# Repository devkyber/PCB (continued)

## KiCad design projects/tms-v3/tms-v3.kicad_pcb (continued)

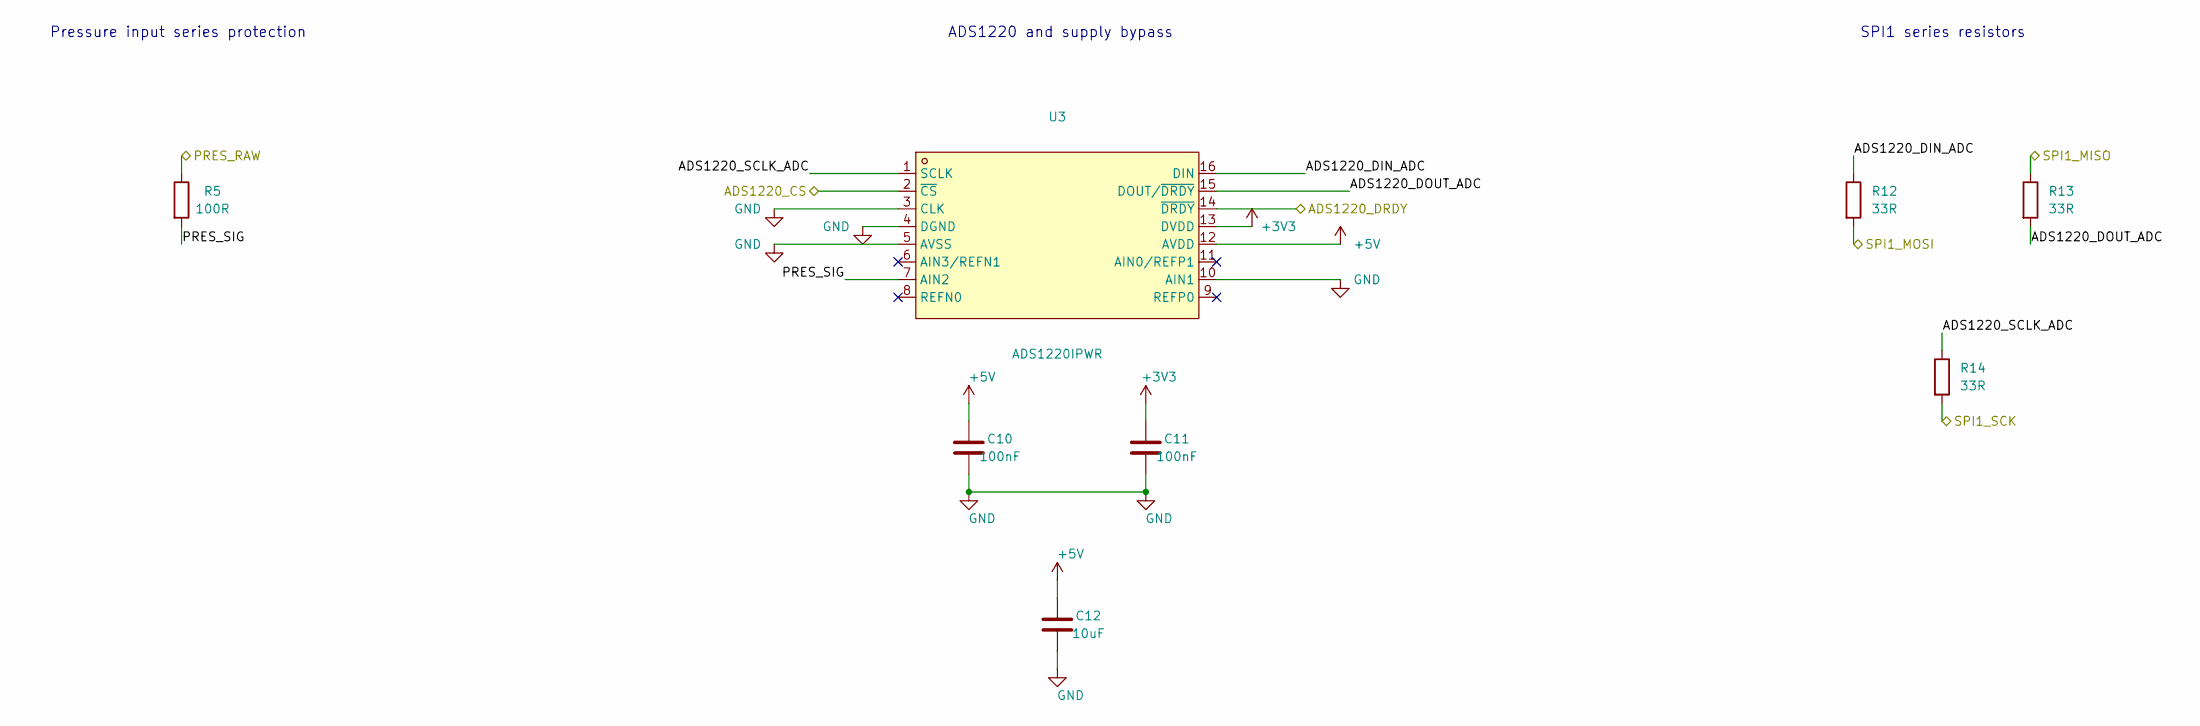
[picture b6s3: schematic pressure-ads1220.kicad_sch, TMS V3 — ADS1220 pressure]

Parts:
C10, C11: 100nF; C_0402_1005Metric
C12: 10uF; C_0805_2012Metric
R5: 100R; R_0402_1005Metric
R12, R13, R14: 33R; R_0402_1005Metric
U3: ADS1220IPWR; TSSOP-16_L5.0-W4.4-P0.65-LS6.4-BL

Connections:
+3V3: C11.1, U3.13 (DVDD); also elsewhere on the board
+5V: C10.1, C12.1, U3.12 (AVDD); also elsewhere on the board
ADS1220 pressure/ADS1220_DIN_ADC: R12.1, U3.16 (DIN)
ADS1220 pressure/ADS1220_DOUT_ADC: R13.2, U3.15 (DOUT/~DRDY)
ADS1220 pressure/ADS1220_SCLK_ADC: R14.1, U3.1 (SCLK)
ADS1220 pressure/PRES_SIG: R5.2, U3.7 (AIN2)
ADS1220_CS: U3.2 (~CS); also elsewhere on the board
ADS1220_DRDY: U3.14 (~DRDY); also elsewhere on the board
GND: C10.2, C11.2, C12.2, U3.3 (CLK), U3.4 (DGND), U3.5 (AVSS), U3.10 (AIN1); also elsewhere on the board
PRES_RAW: R5.1; also elsewhere on the board
SPI1_MISO: R13.1; also elsewhere on the board
SPI1_MOSI: R12.2; also elsewhere on the board
SPI1_SCK: R14.2; also elsewhere on the board

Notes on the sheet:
Pressure input series protection
ADS1220 and supply bypass
SPI1 series resistors

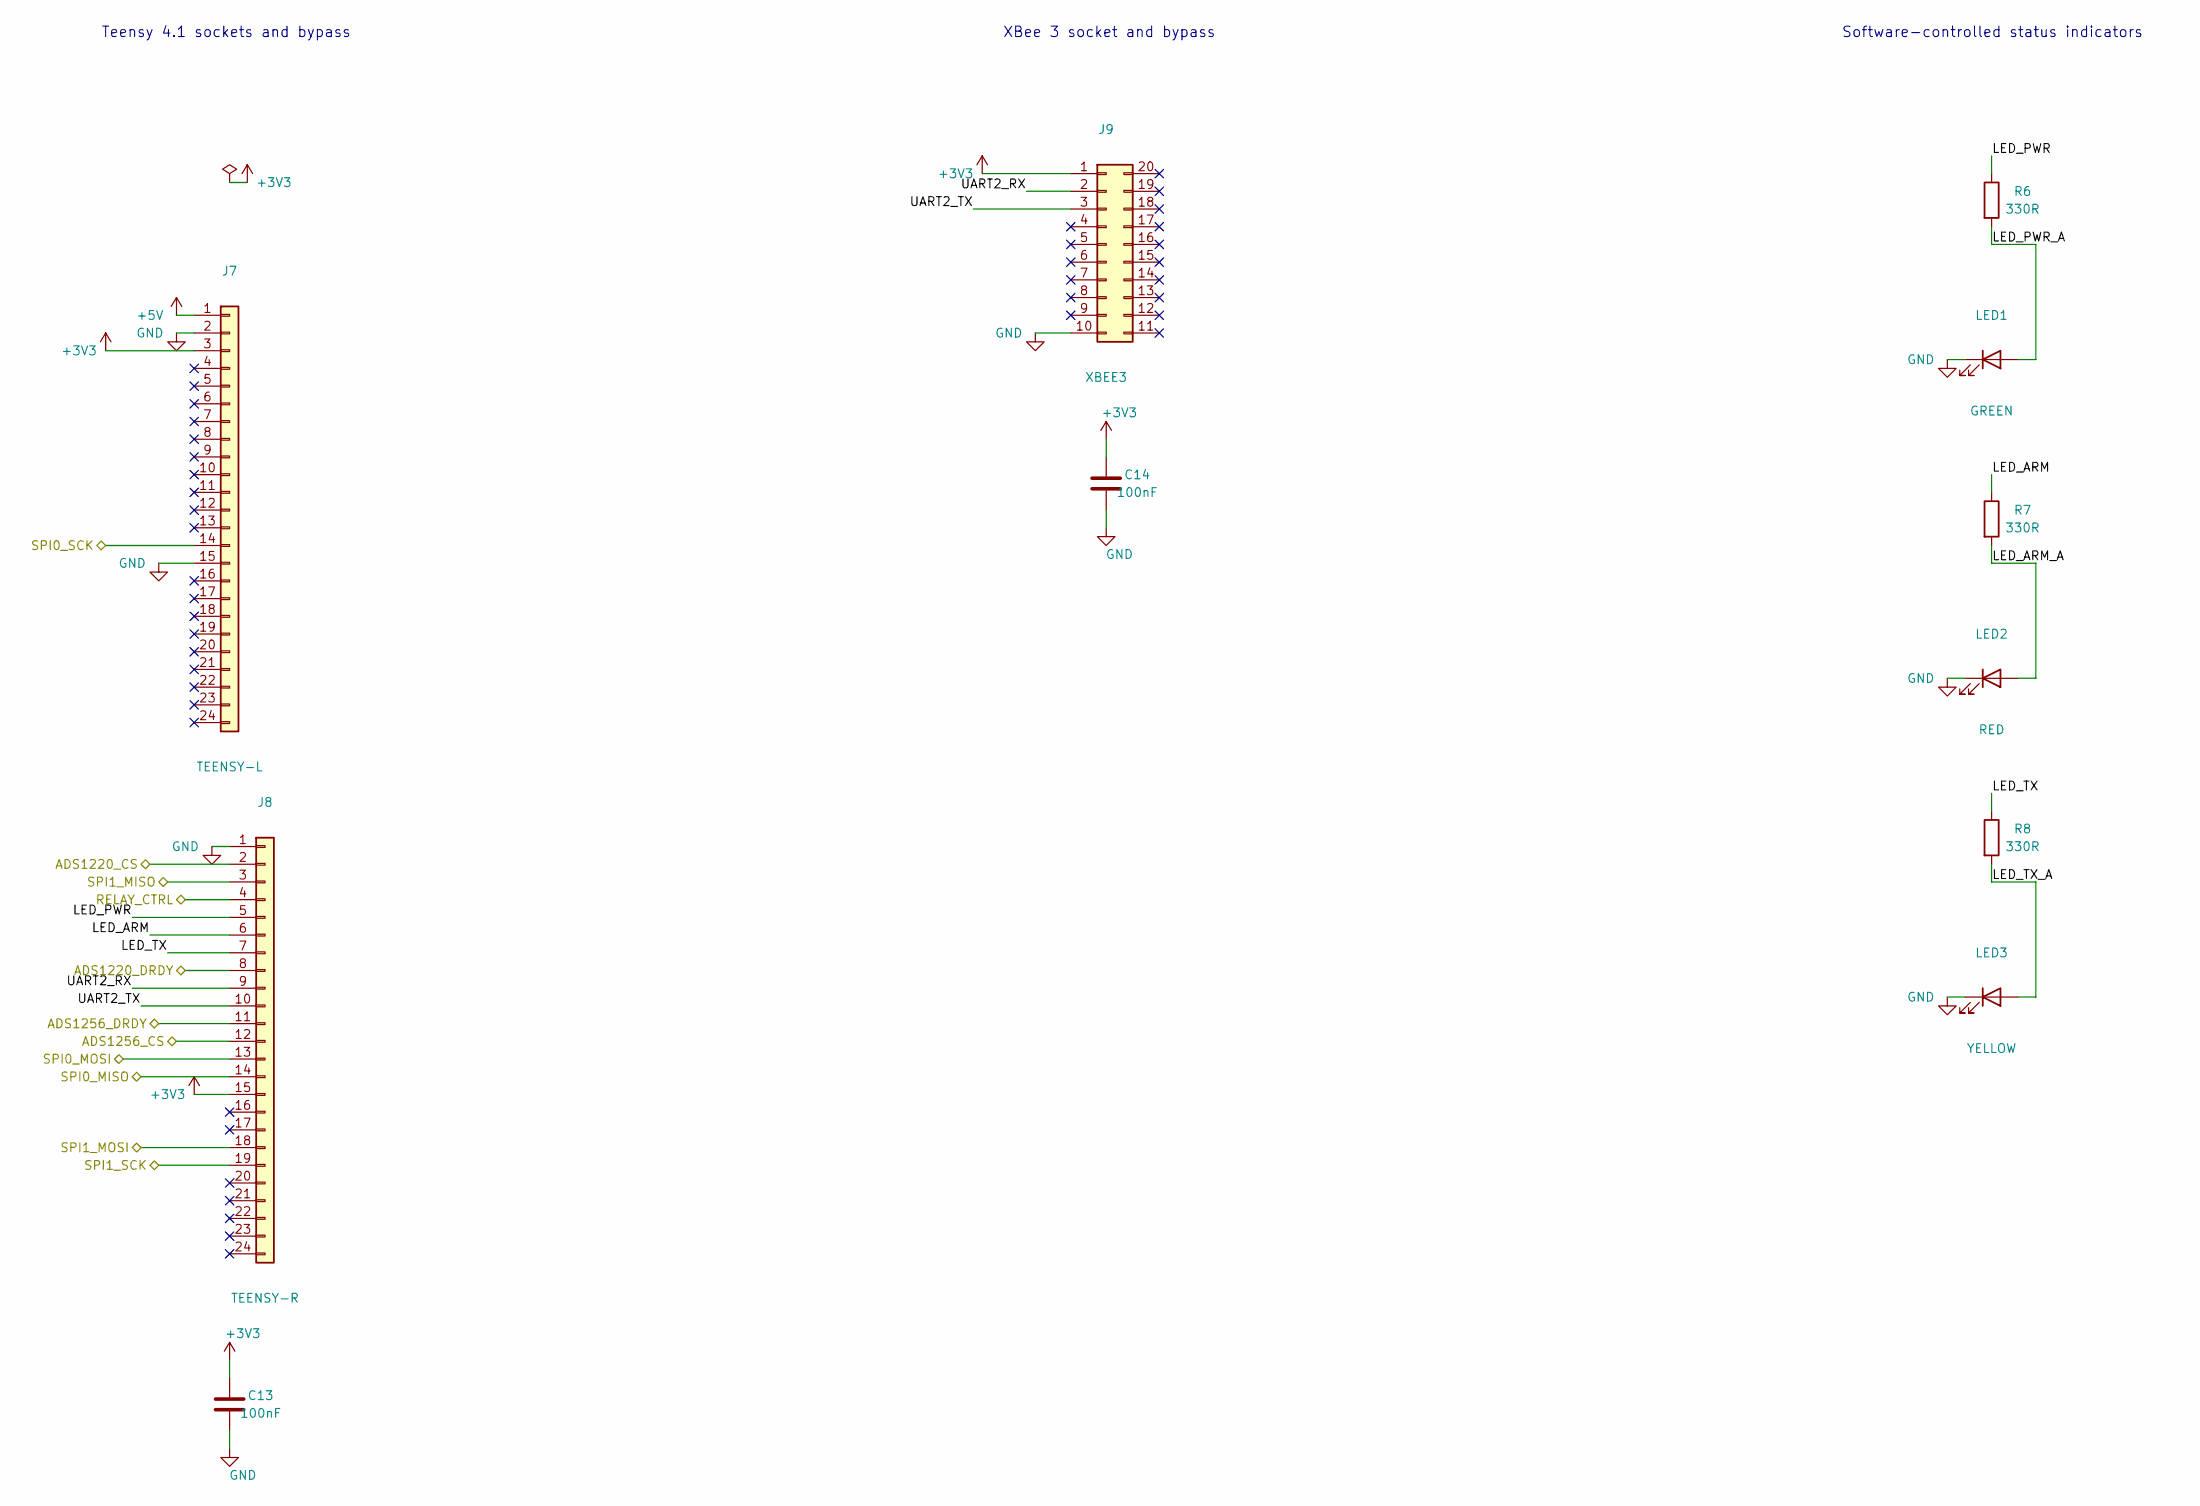
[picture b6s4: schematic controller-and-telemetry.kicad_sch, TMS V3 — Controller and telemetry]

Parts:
C13, C14: 100nF; C_0603_1608Metric
J7: TEENSY-L; PinSocket_1x24_P2.54mm_Vertical
J8: TEENSY-R; PinSocket_1x24_P2.54mm_Vertical
J9: XBEE3; XBee_THT_20pin_P2.00mm
LED1: GREEN; LED_0603_1608Metric
LED2: RED; LED_0603_1608Metric
LED3: YELLOW; LED_0603_1608Metric
R6, R7, R8: 330R; R_0402_1005Metric

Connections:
+3V3: C13.1, C14.1, J7.3, J8.15, J9.1; also elsewhere on the board
+5V: J7.1; also elsewhere on the board
ADS1220_CS: J8.2; also elsewhere on the board
ADS1220_DRDY: J8.8; also elsewhere on the board
ADS1256_CS: J8.12; also elsewhere on the board
ADS1256_DRDY: J8.11; also elsewhere on the board
Controller and telemetry/LED_ARM: J8.6, R7.1
Controller and telemetry/LED_ARM_A: LED2.2 (A), R7.2
Controller and telemetry/LED_PWR: J8.5, R6.1
Controller and telemetry/LED_PWR_A: LED1.2 (A), R6.2
Controller and telemetry/LED_TX: J8.7, R8.1
Controller and telemetry/LED_TX_A: LED3.2 (A), R8.2
Controller and telemetry/UART2_RX: J8.9, J9.2
Controller and telemetry/UART2_TX: J8.10, J9.3
GND: C13.2, C14.2, J7.2, J7.15, J8.1, J9.10, LED1.1 (K), LED2.1 (K), LED3.1 (K); also elsewhere on the board
RELAY_CTRL: J8.4; also elsewhere on the board
SPI0_MISO: J8.14; also elsewhere on the board
SPI0_MOSI: J8.13; also elsewhere on the board
SPI0_SCK: J7.14; also elsewhere on the board
SPI1_MISO: J8.3; also elsewhere on the board
SPI1_MOSI: J8.18; also elsewhere on the board
SPI1_SCK: J8.19; also elsewhere on the board

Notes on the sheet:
Teensy 4.1 sockets and bypass
XBee 3 socket and bypass
Software-controlled status indicators

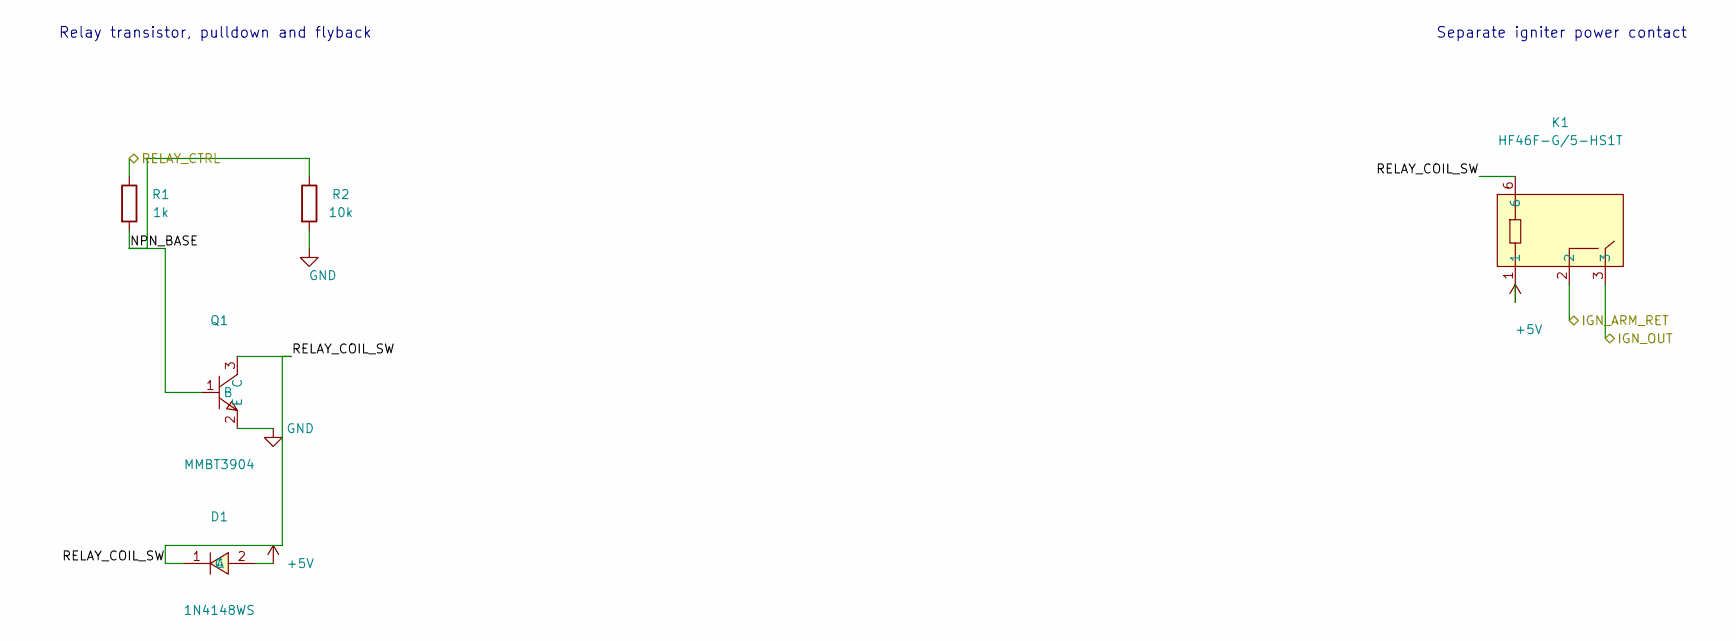
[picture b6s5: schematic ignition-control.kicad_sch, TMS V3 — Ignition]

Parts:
D1: 1N4148WS; SOD-323_L1.8-W1.3-LS2.5-RD-1
K1: HF46F-G/5-HS1T; RELAYS-TH_HF46F-G-XX-HS1-XXX
Q1: MMBT3904; SOT-23-3_L2.9-W1.3-P1.90-LS2.4-BR
R1: 1k; R_0402_1005Metric
R2: 10k; R_0402_1005Metric

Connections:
+5V: D1.2 (A), K1.1; also elsewhere on the board
GND: Q1.2 (E), R2.2; also elsewhere on the board
IGN_ARM_RET: K1.2; also elsewhere on the board
IGN_OUT: K1.3; also elsewhere on the board
Ignition/NPN_BASE: Q1.1 (B), R1.2, R2.1
Ignition/RELAY_COIL_SW: D1.1 (C), K1.6, Q1.3 (C)
RELAY_CTRL: R1.1; also elsewhere on the board

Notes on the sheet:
Relay transistor, pulldown and flyback
Separate igniter power contact

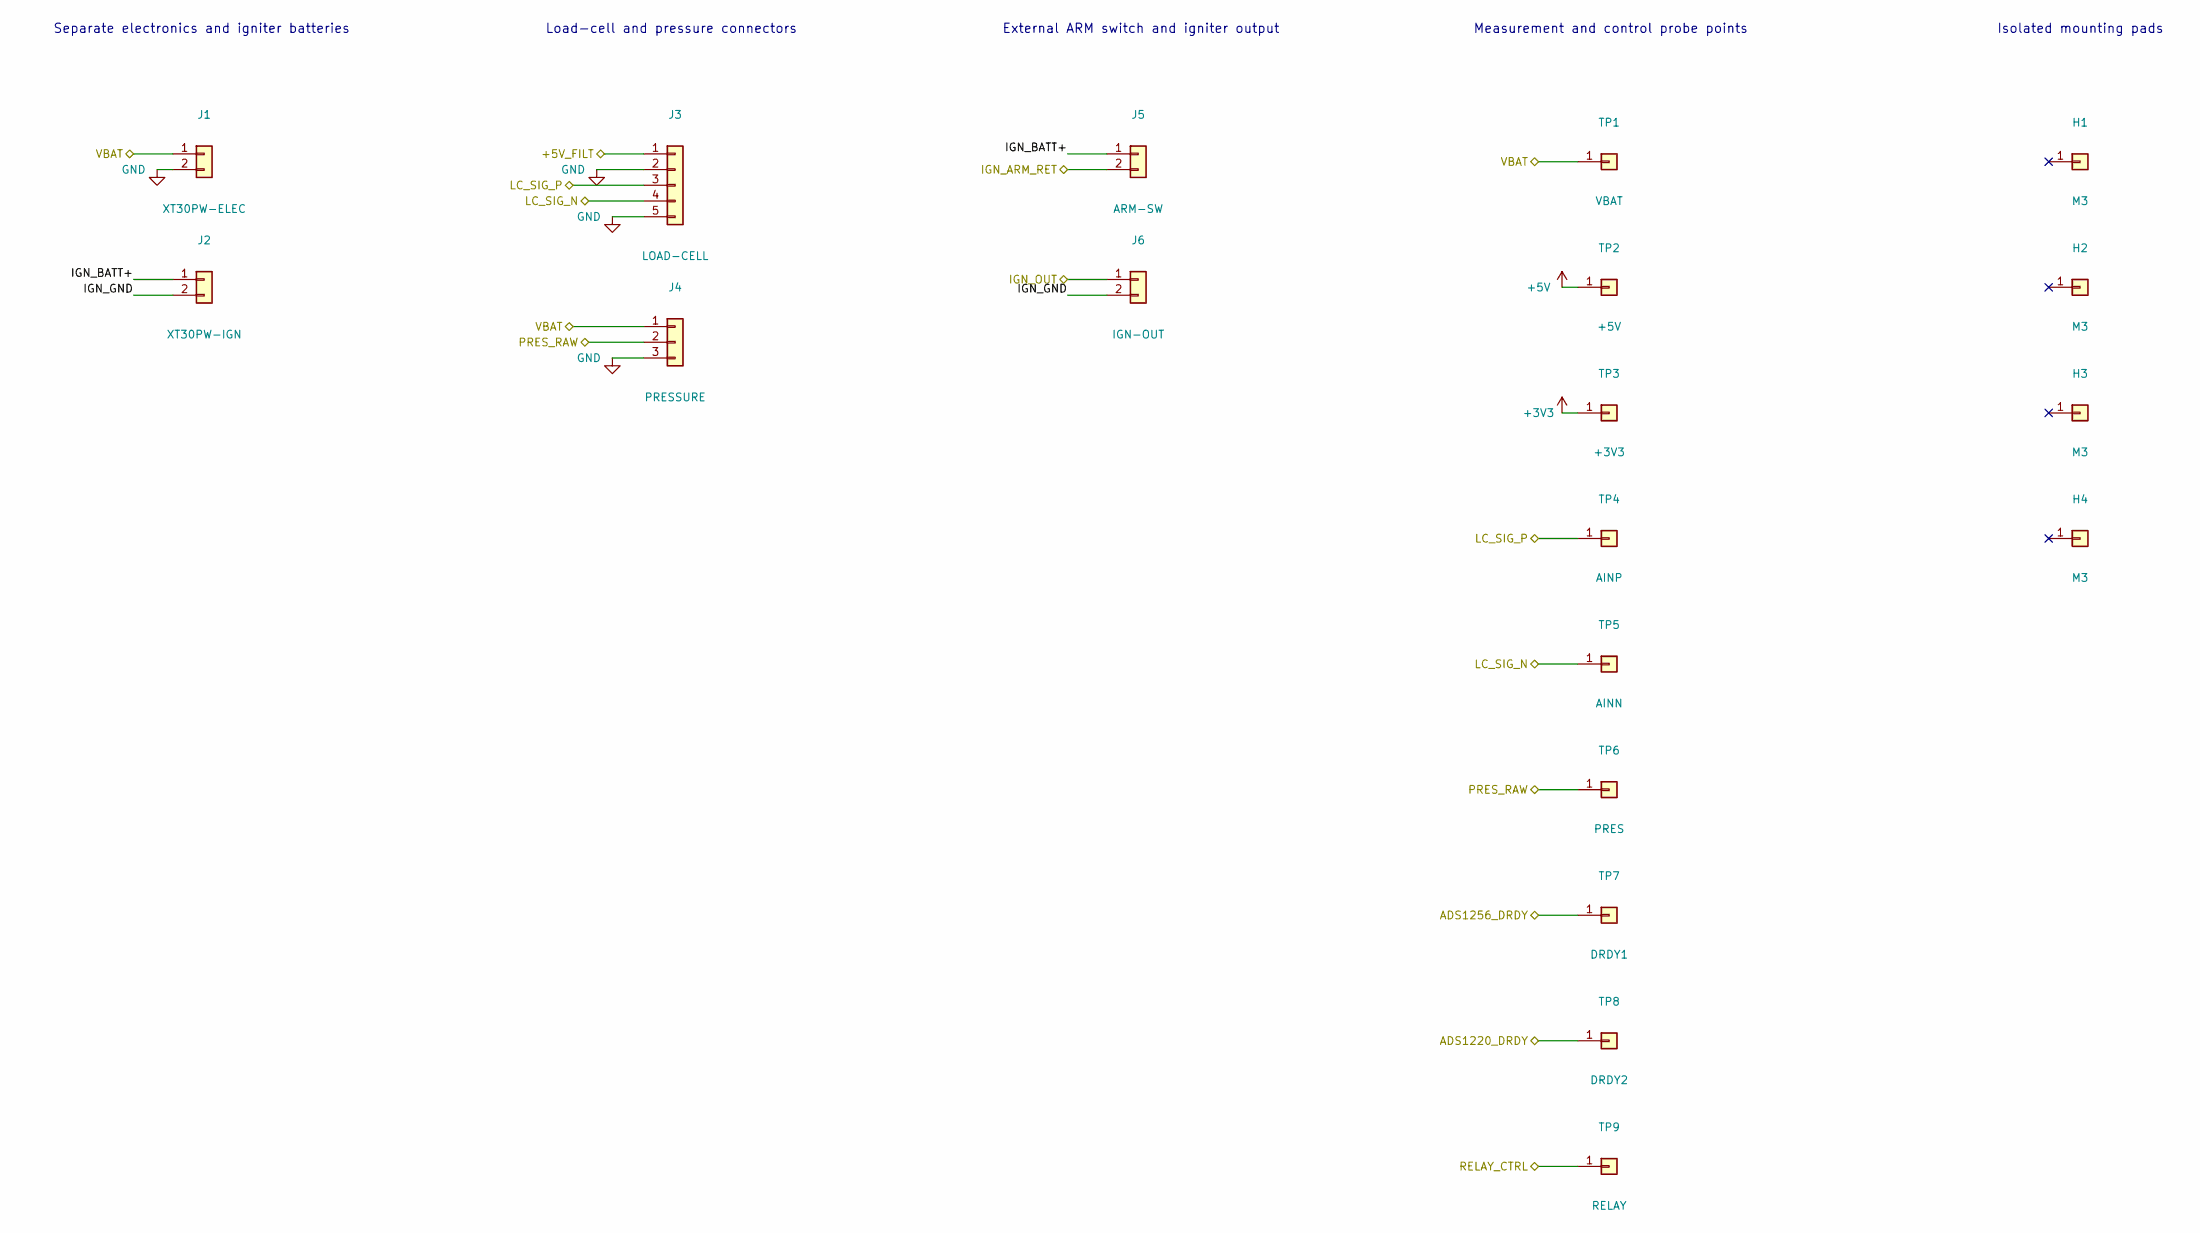
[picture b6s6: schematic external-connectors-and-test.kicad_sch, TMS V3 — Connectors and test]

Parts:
H1, H2, H3, H4: M3; MountingHole_3.2mm_M3_Pad
J1: XT30PW-ELEC; AMASS_XT30PW-F_1x02_P2.50mm_Horizontal
J2: XT30PW-IGN; AMASS_XT30PW-F_1x02_P2.50mm_Horizontal
J3: LOAD-CELL; JST_XH_B5B-XH-A_1x05_P2.50mm_Vertical
J4: PRESSURE; JST_XH_B3B-XH-A_1x03_P2.50mm_Vertical
J5: ARM-SW; TerminalBlock_Phoenix_MKDS-1,5-2-5.08_1x02_P5.08mm_Horizont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
J6: IGN-OUT; AMASS_XT60-F_1x02_P7.20mm_Vertical
TP1: VBAT; TestPoint_Pad_1.0x1.0mm
TP2: +5V; TestPoint_Pad_1.0x1.0mm
TP3: +3V3; TestPoint_Pad_1.0x1.0mm
TP4: AINP; TestPoint_Pad_1.0x1.0mm
TP5: AINN; TestPoint_Pad_1.0x1.0mm
TP6: PRES; TestPoint_Pad_1.0x1.0mm
TP7: DRDY1; TestPoint_Pad_1.0x1.0mm
TP8: DRDY2; TestPoint_Pad_1.0x1.0mm
TP9: RELAY; TestPoint_Pad_1.0x1.0mm

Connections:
+3V3: TP3.1; also elsewhere on the board
+5V: TP2.1; also elsewhere on the board
+5V_FILT: J3.1; also elsewhere on the board
ADS1220_DRDY: TP8.1; also elsewhere on the board
ADS1256_DRDY: TP7.1; also elsewhere on the board
Connectors and test/IGN_BATT+: J2.1, J5.1
Connectors and test/IGN_GND: J2.2, J6.2
GND: J1.2, J3.2, J3.5, J4.3; also elsewhere on the board
IGN_ARM_RET: J5.2; also elsewhere on the board
IGN_OUT: J6.1; also elsewhere on the board
LC_SIG_N: J3.4, TP5.1; also elsewhere on the board
LC_SIG_P: J3.3, TP4.1; also elsewhere on the board
PRES_RAW: J4.2, TP6.1; also elsewhere on the board
RELAY_CTRL: TP9.1; also elsewhere on the board
VBAT: J1.1, J4.1, TP1.1; also elsewhere on the board

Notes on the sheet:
Separate electronics and igniter batteries
Load-cell and pressure connectors
External ARM switch and igniter output
Measurement and control probe points
Isolated mounting pads

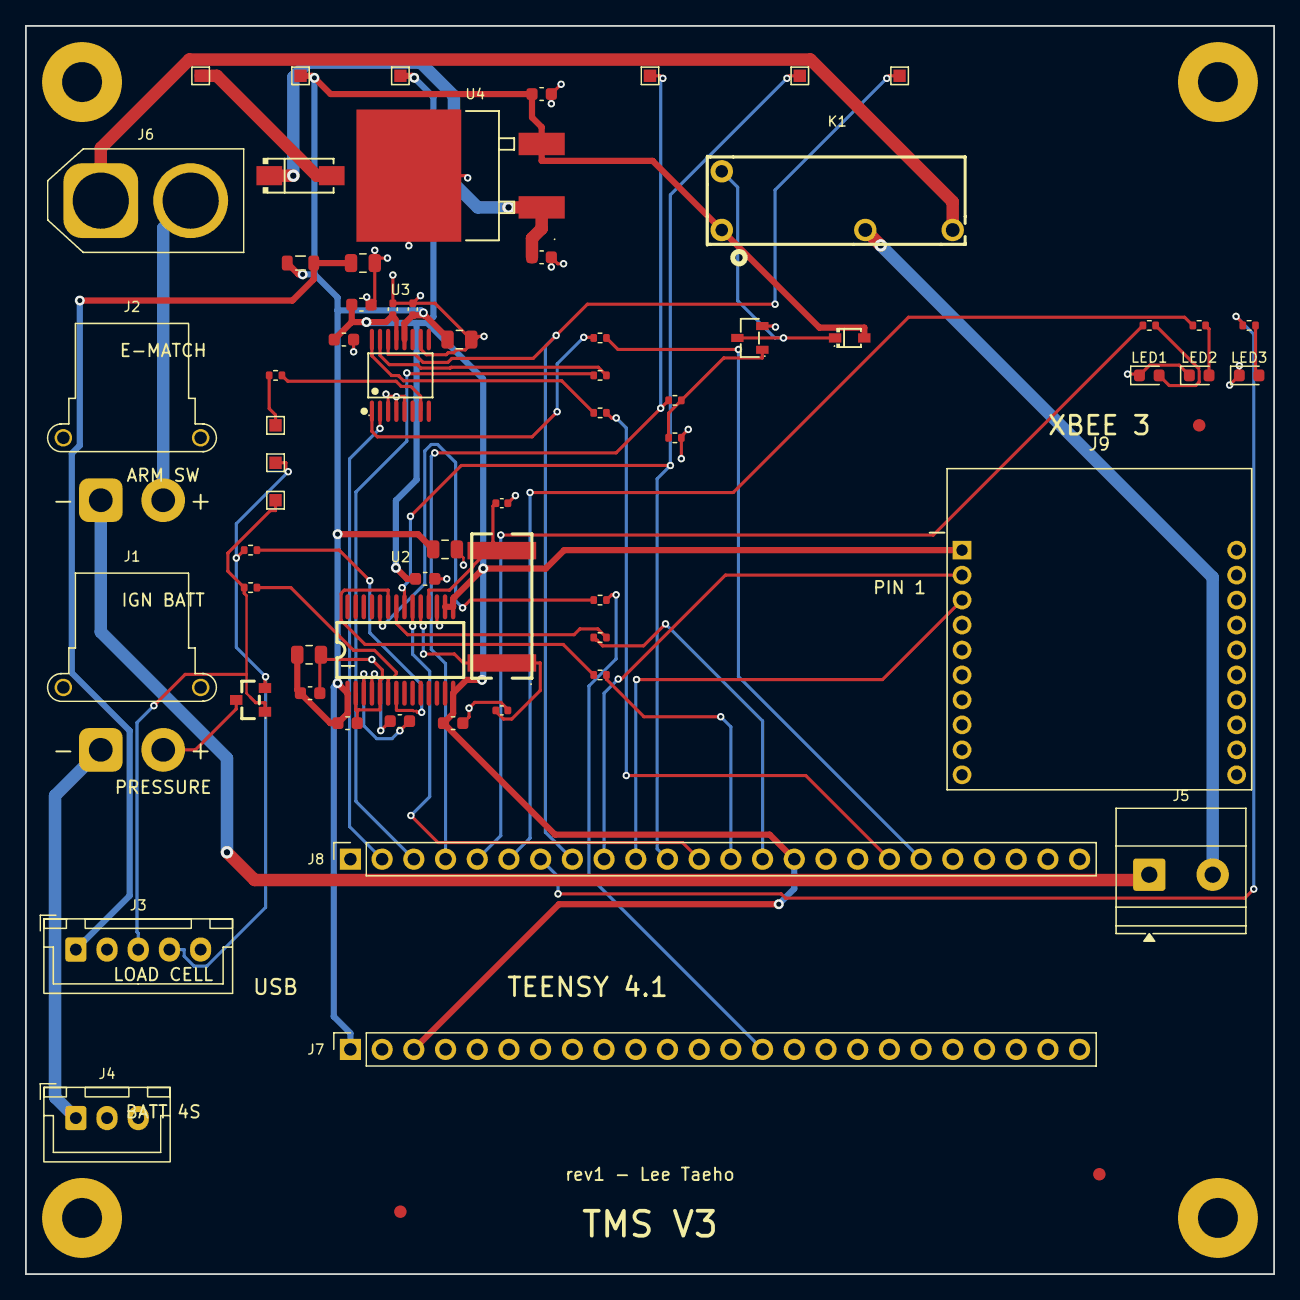
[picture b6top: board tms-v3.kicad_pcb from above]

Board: 2 copper layers, 100.0 x 100.0 mm, 69 parts (0 on the bottom side), 47 nets.

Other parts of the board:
FID1, FID2, FID3: FIDUCIAL; Fiducial_1mm_Mask3mm

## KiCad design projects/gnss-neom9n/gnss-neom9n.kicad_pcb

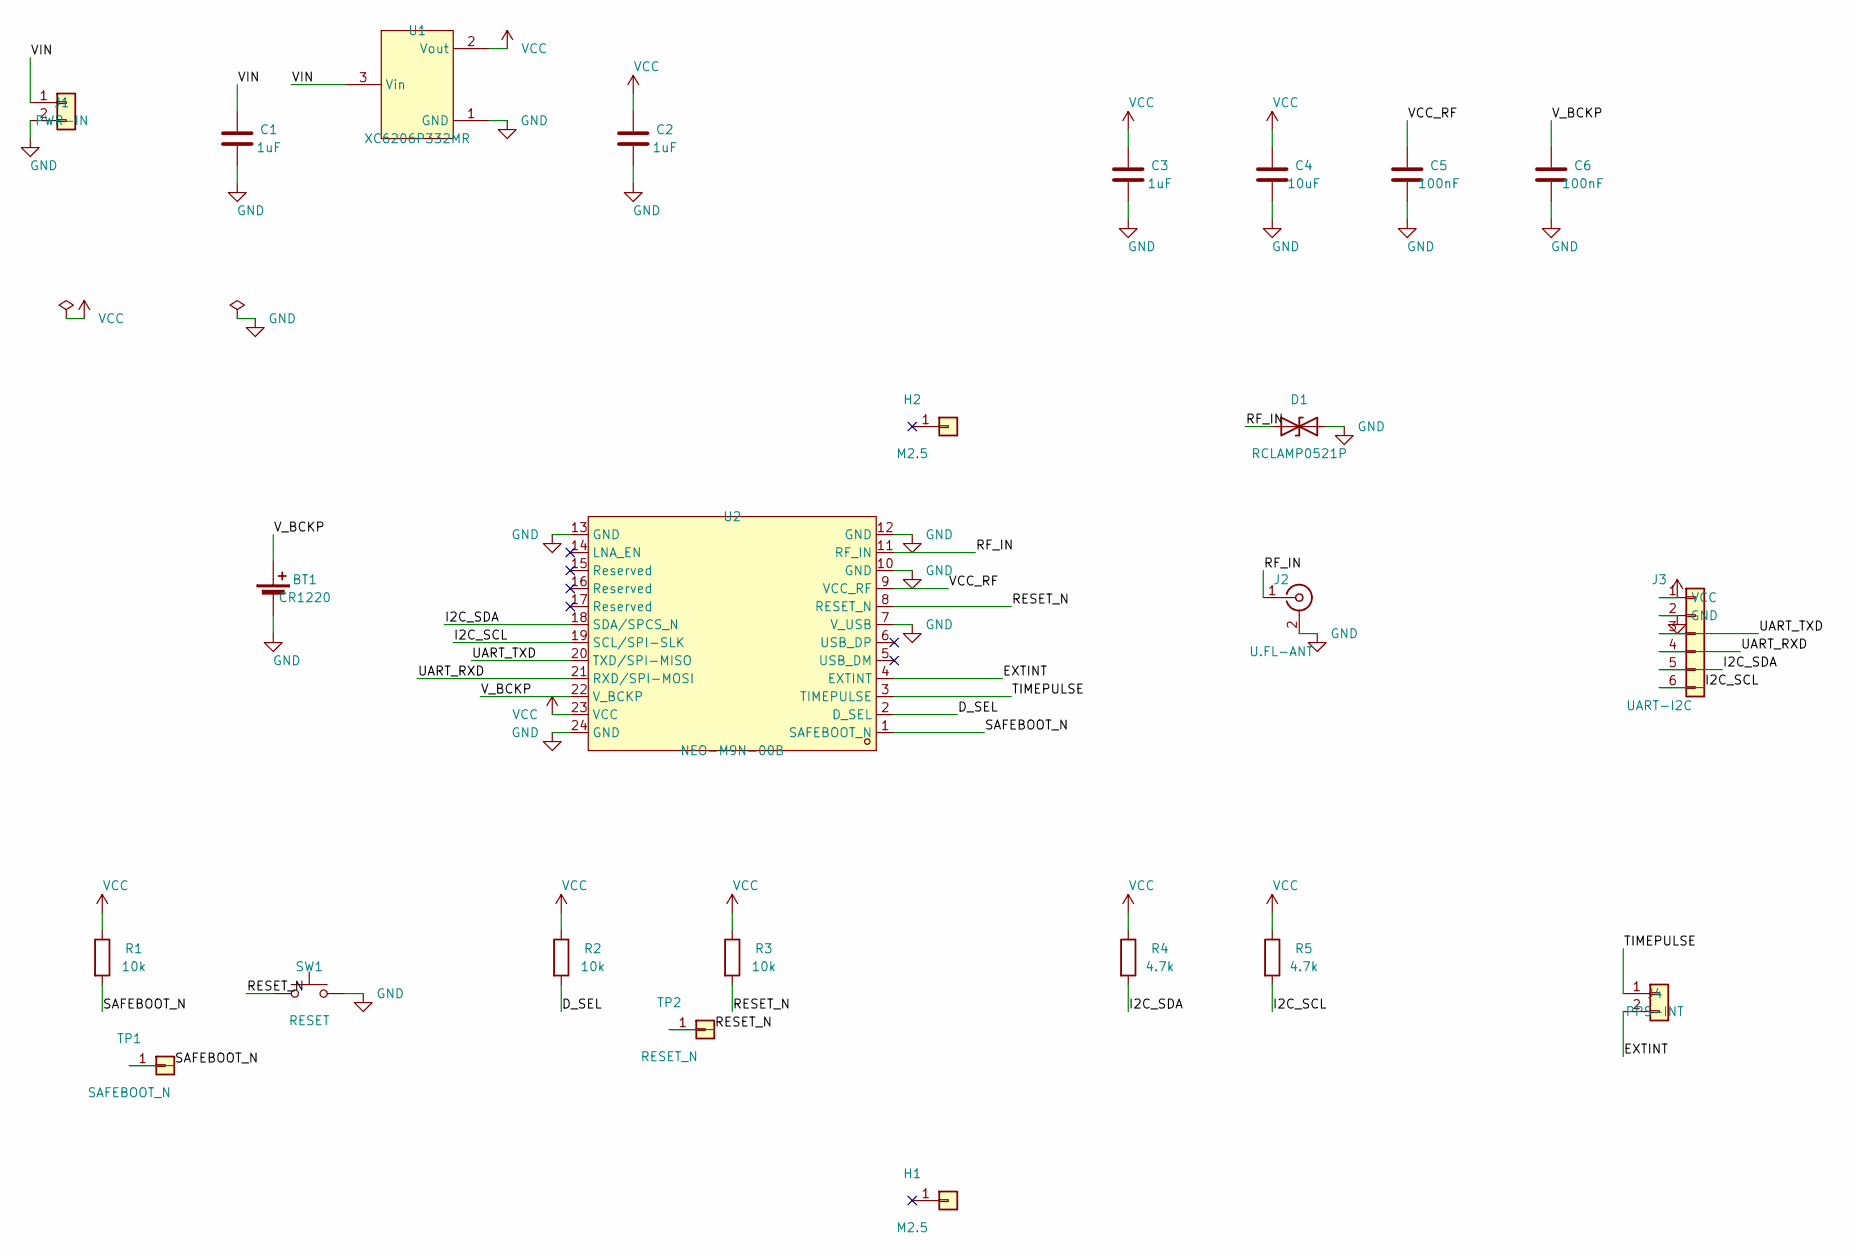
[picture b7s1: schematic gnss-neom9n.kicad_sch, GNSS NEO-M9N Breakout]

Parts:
BT1: CR1220; Battery_Panasonic_CR1220-VCN_Vertical_CircularHoles
C1, C2, C3: 1uF; C_0603_1608Metric
C4: 10uF; C_0805_2012Metric
C5, C6: 100nF; C_0603_1608Metric
D1: RCLAMP0521P; D_0402_1005Metric
H1, H2: M2.5; MountingHole_2.7mm_M2.5_Pad
J1: PWR-IN; PinHeader_1x02_P2.54mm_Vertical
J2: U.FL-ANT; U.FL_Hirose_U.FL-R-SMT-1_Vertical
J3: UART-I2C; PinHeader_1x06_P2.54mm_Vertical
J4: PPS-INT; PinHeader_1x02_P2.54mm_Vertical
R1, R2, R3: 10k; R_0402_1005Metric
R4, R5: 4.7k; R_0402_1005Metric
SW1: RESET; SW_SPST_B3U-1000P
TP1: SAFEBOOT_N; TestPoint_Pad_1.0x1.0mm
TP2: RESET_N; TestPoint_Pad_1.0x1.0mm
U1: XC6206P332MR; SOT-23-3_L2.9-W1.6-P1.90-LS2.8-BR
U2: NEO-M9N-00B; GPSM-SMD_24P-L16.0-W12.2-P1.10-BL

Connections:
D_SEL: R2.2, U2.2 (D_SEL)
EXTINT: J4.2, U2.4 (EXTINT)
GND: BT1.2 (-), C1.2, C2.2, C3.2, C4.2, C5.2, C6.2, D1.2 (A2), J1.2, J2.2 (Ext), J3.2, SW1.2, U1.1 (GND), U2.7 (V_USB), U2.10 (GND), U2.12 (GND), U2.13 (GND), U2.24 (GND)
I2C_SCL: J3.6, R5.2, U2.19 (SCL/SPI-SLK)
I2C_SDA: J3.5, R4.2, U2.18 (SDA/SPCS_N)
RESET_N: R3.2, SW1.1, TP2.1, U2.8 (RESET_N)
RF_IN: D1.1 (A1), J2.1 (In), U2.11 (RF_IN)
SAFEBOOT_N: R1.2, TP1.1, U2.1 (SAFEBOOT_N)
TIMEPULSE: J4.1, U2.3 (TIMEPULSE)
UART_RXD: J3.4, U2.21 (RXD/SPI-MOSI)
UART_TXD: J3.3, U2.20 (TXD/SPI-MISO)
VCC: C2.1, C3.1, C4.1, J3.1, R1.1, R2.1, R3.1, R4.1, R5.1, U1.2 (Vout), U2.23 (VCC)
VCC_RF: C5.1, U2.9 (VCC_RF)
VIN: C1.1, J1.1, U1.3 (Vin)
V_BCKP: BT1.1 (+), C6.1, U2.22 (V_BCKP)

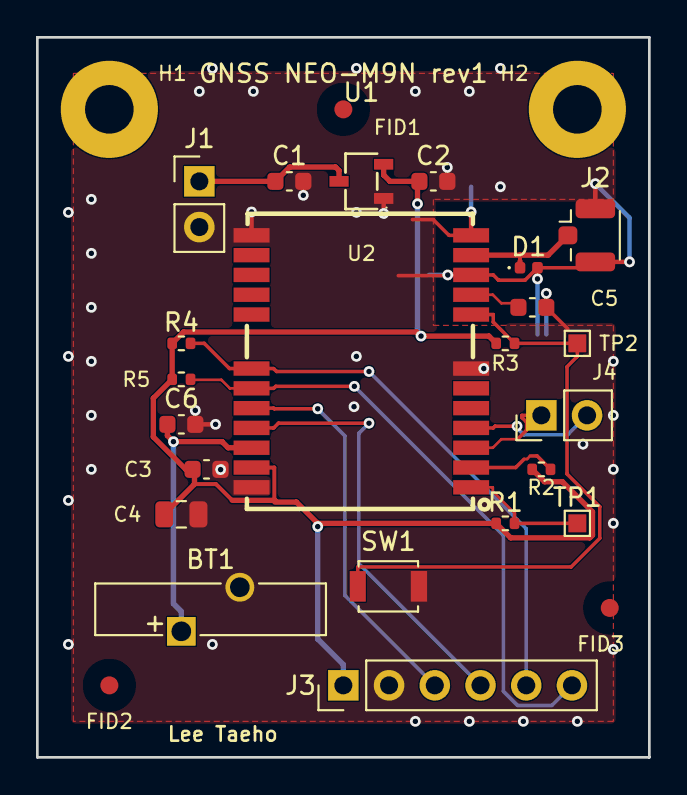
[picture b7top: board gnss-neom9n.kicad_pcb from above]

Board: 2 copper layers, 34.0 x 40.0 mm, 27 parts (0 on the bottom side), 15 nets.

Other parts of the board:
FID1, FID2, FID3: FIDUCIAL; Fiducial_1mm_Mask3mm

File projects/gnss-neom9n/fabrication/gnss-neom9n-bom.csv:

Comment,Designator,Footprint,LCSC Part #
100nF,"C5,C6",C_0603_1608Metric,C14663
10k,"R1,R2,R3",R_0402_1005Metric,C25744
10uF,C4,C_0805_2012Metric,C15850
1uF,"C1,C2,C3",C_0603_1608Metric,C15849
4.7k,"R4,R5",R_0402_1005Metric,C25900
CR1220,BT1,Battery_Panasonic_CR1220-VCN_Vertical_CircularHoles,
NEO-M9N-00B,U2,GPSM-SMD_24P-L16.0-W12.2-P1.10-BL,C5119087
PPS-INT,J4,PinHeader_1x02_P2.54mm_Vertical,C492401
PWR-IN,J1,PinHeader_1x02_P2.54mm_Vertical,C492401
RCLAMP0521P,D1,D_0402_1005Metric,C117554
RESET,SW1,SW_SPST_B3U-1000P,C231329
U.FL-ANT,J2,U.FL_Hirose_U.FL-R-SMT-1_Vertical,C88374
UART-I2C,J3,PinHeader_1x06_P2.54mm_Vertical,C37208
XC6206P332MR,U1,SOT-23-3_L2.9-W1.6-P1.90-LS2.8-BR,C5446

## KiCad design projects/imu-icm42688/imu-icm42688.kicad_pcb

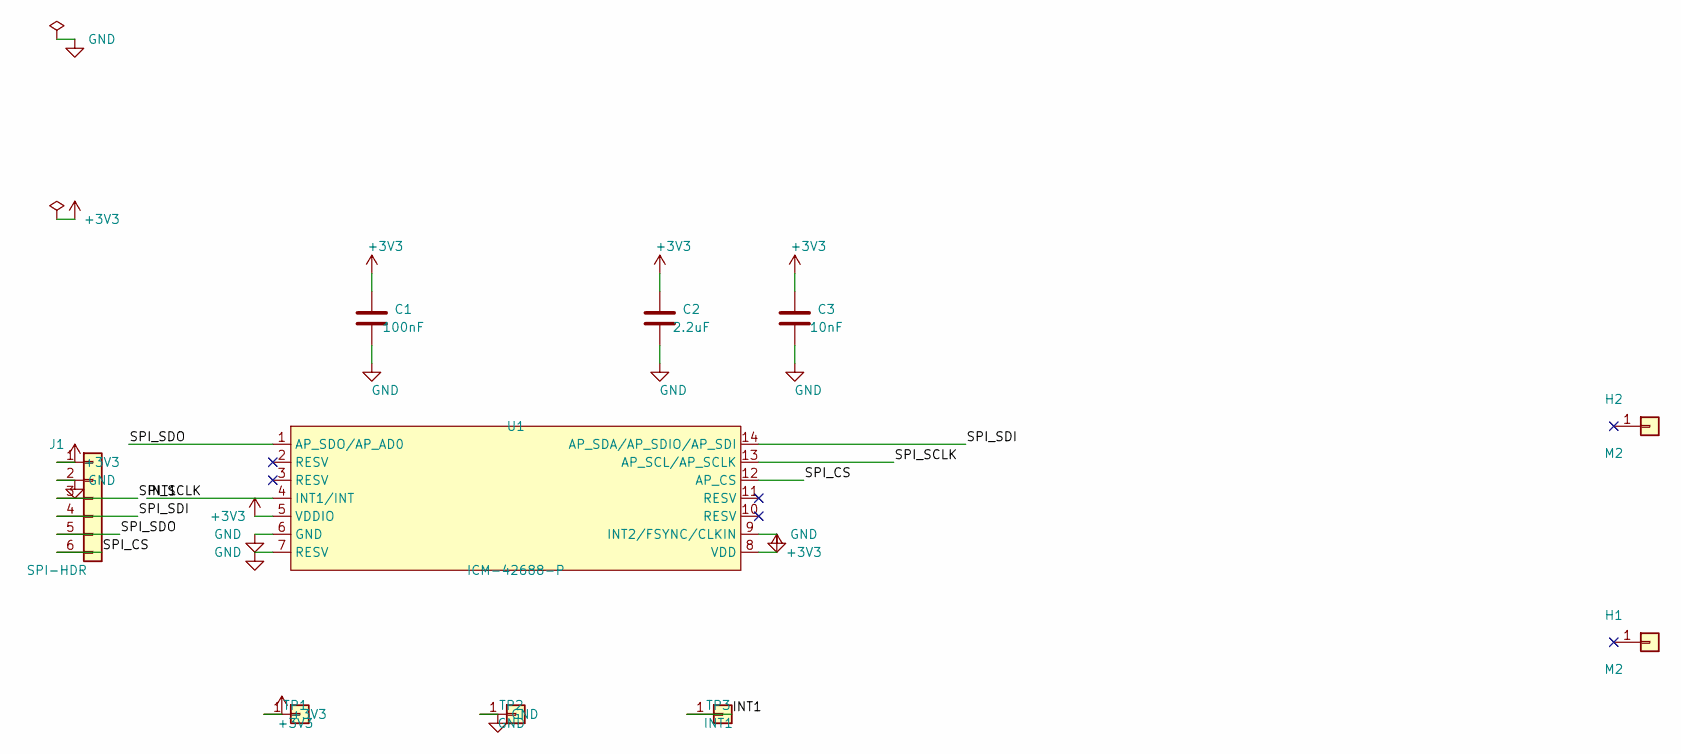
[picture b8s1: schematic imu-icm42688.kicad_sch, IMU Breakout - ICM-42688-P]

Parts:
C1: 100nF; C_0402_1005Metric
C2: 2.2uF; C_0603_1608Metric
C3: 10nF; C_0402_1005Metric
H1, H2: M2; MountingHole_2.2mm_M2_Pad
J1: SPI-HDR; PinHeader_1x06_P2.54mm_Vertical
TP1: +3V3; TestPoint_Pad_1.0x1.0mm
TP2: GND; TestPoint_Pad_1.0x1.0mm
TP3: INT1; TestPoint_Pad_1.0x1.0mm
U1: ICM-42688-P; LGA-14_L3.0-W2.5-P0.50-TL

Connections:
+3V3: C1.1, C2.1, C3.1, J1.1, TP1.1, U1.5 (VDDIO), U1.8 (VDD)
GND: C1.2, C2.2, C3.2, J1.2, TP2.1, U1.6 (GND), U1.7 (RESV), U1.9 (INT2/FSYNC/CLKIN)
INT1: TP3.1, U1.4 (INT1/INT)
SPI_CS: J1.6, U1.12 (AP_CS)
SPI_SCLK: J1.3, U1.13 (AP_SCL/AP_SCLK)
SPI_SDI: J1.4, U1.14 (AP_SDA/AP_SDIO/AP_SDI)
SPI_SDO: J1.5, U1.1 (AP_SDO/AP_AD0)

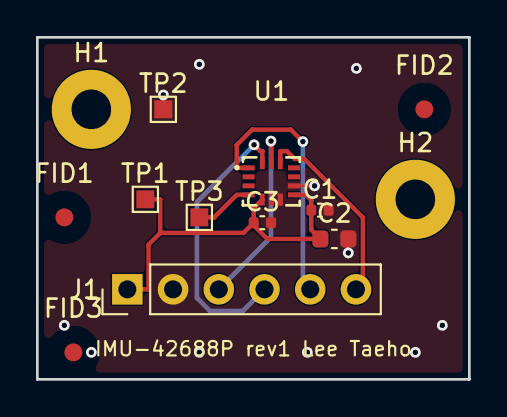
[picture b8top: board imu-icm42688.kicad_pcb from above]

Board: 2 copper layers, 24.0 x 19.0 mm, 13 parts (0 on the bottom side), 7 nets.

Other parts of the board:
FID1, FID2, FID3: FIDUCIAL; Fiducial_1mm_Mask3mm

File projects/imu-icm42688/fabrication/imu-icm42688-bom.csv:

Comment,Designator,Footprint,LCSC Part #
100nF,C1,C_0402_1005Metric,C307331
10nF,C3,C_0402_1005Metric,C15195
2.2uF,C2,C_0603_1608Metric,C23630
ICM-42688-P,U1,LGA-14_L3.0-W2.5-P0.50-TL,C1850418
SPI-HDR,J1,PinHeader_1x06_P2.54mm_Vertical,C37208
